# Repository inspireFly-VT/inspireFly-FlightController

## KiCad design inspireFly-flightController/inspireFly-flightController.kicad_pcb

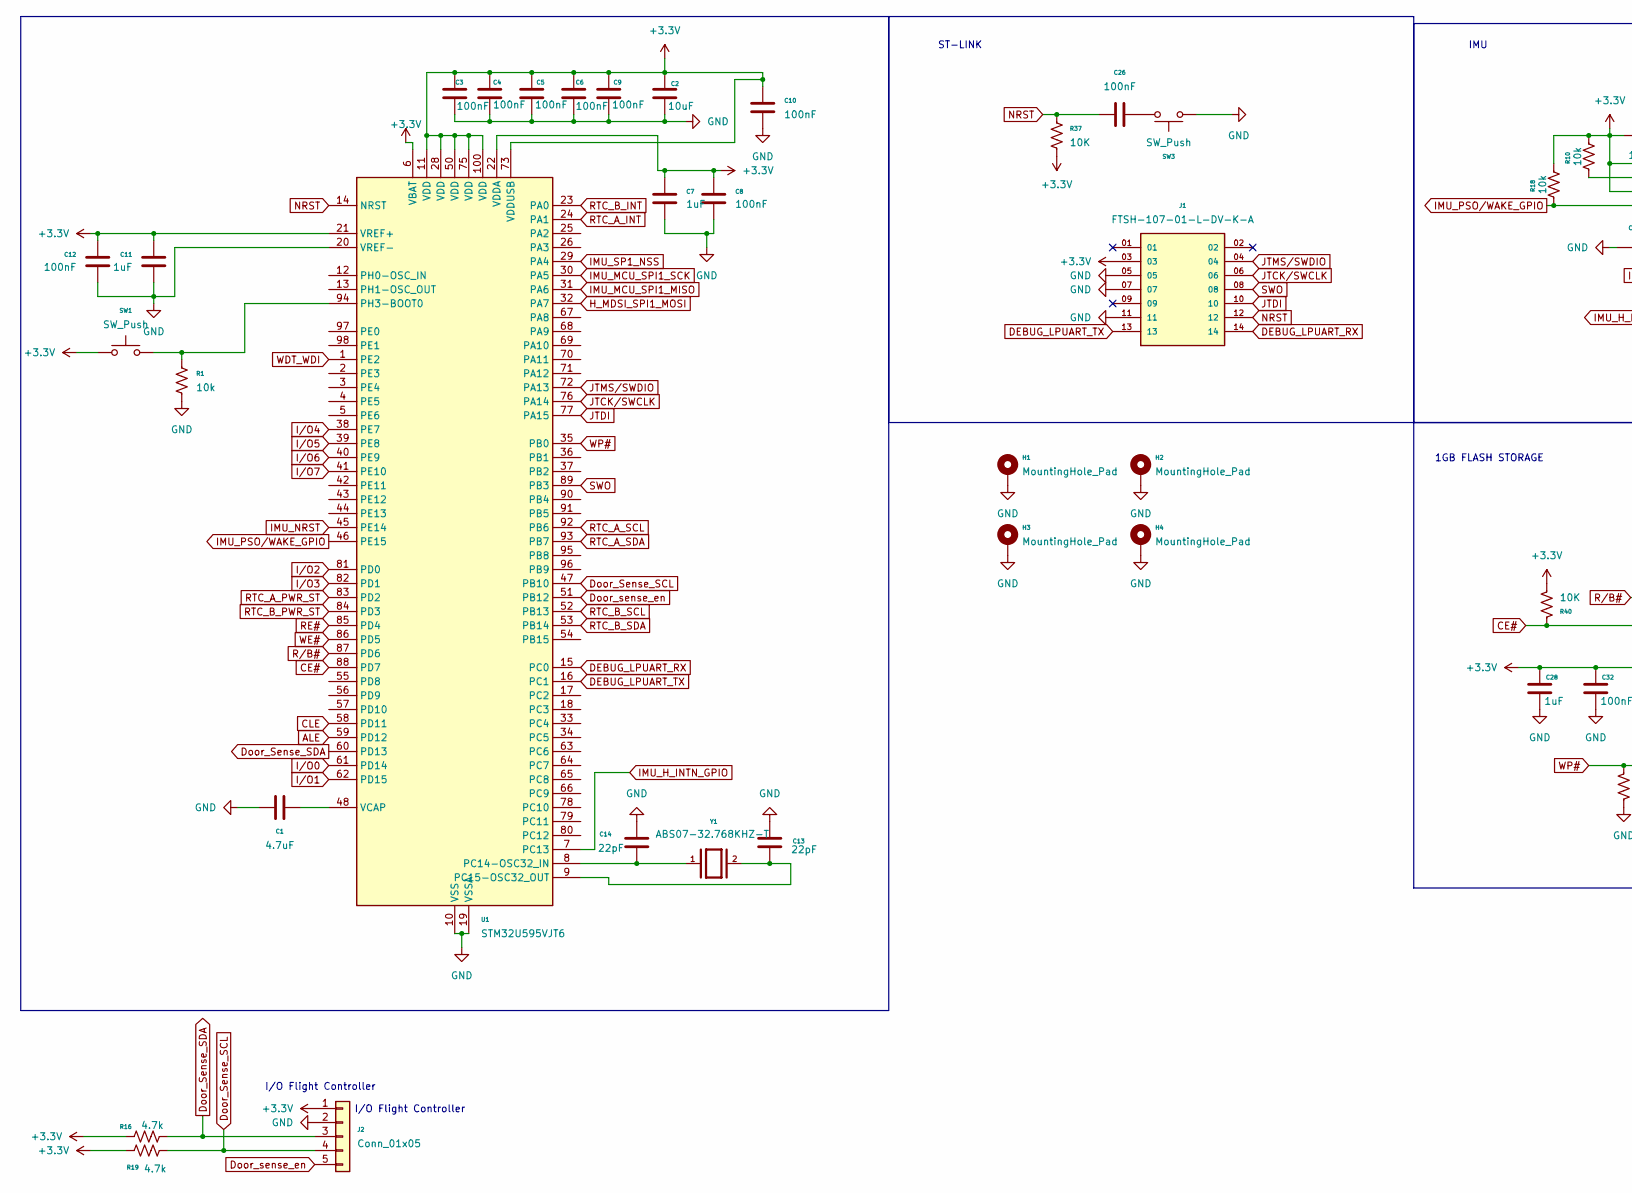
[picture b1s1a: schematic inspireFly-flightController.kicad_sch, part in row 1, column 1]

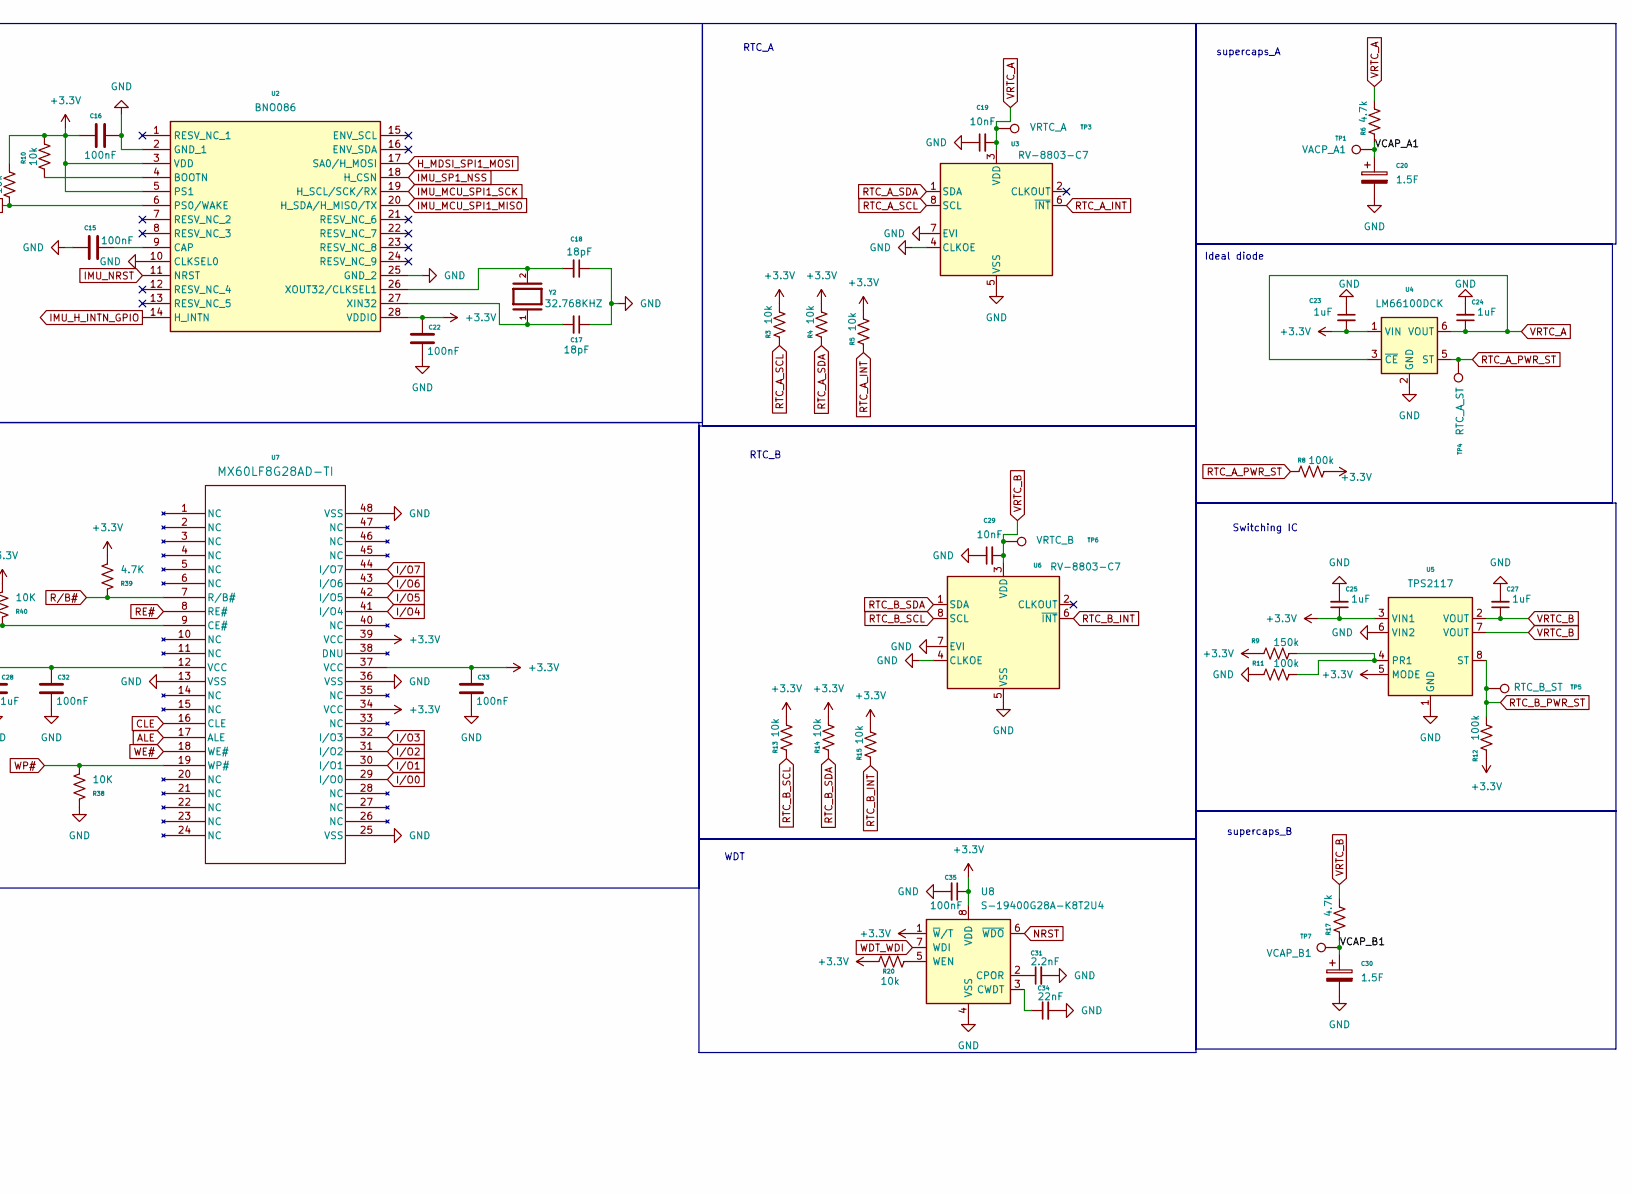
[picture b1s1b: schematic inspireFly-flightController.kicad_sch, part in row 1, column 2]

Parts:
C1: 4.7uF; C_0603_1608Metric
C2: 10uF; C_0603_1608Metric
C3, C4, C5, C6, C8, C9, C10, C12, C15, C16, C22, C26, C32, C33, C35: 100nF; C_0402_1005Metric_Pad0.74x0.62mm_HandSolder
C7, C11, C23, C24, C25, C27, C28: 1uF; C_0402_1005Metric_Pad0.74x0.62mm_HandSolder
C13, C14: 22pF; C_0402_1005Metric_Pad0.74x0.62mm_HandSolder
C17, C18: 18pF; C_0402_1005Metric_Pad0.74x0.62mm_HandSolder
C19, C29: 10nF; C_0402_1005Metric_Pad0.74x0.62mm_HandSolder
C20, C30: 1.5F; SUPERCAP_KR-5R5H155-R
C31: 2.2nF; C_0402_1005Metric_Pad0.74x0.62mm_HandSolder
C34: 22nF; C_0402_1005Metric_Pad0.74x0.62mm_HandSolder
H1, H2, H3, H4: MountingHole_Pad; MountingHole_2.2mm_M2_Pad_TopBottom
J1: FTSH-107-01-L-DV-K-A; SAMTEC_FTSH-107-01-L-DV-K-A; PARTREV H
J2: Conn_01x05; PinSocket_1x05_P2.54mm_Vertical
R1, R3, R4, R5, R10, R13, R14, R15, R18, R20: 10k; R_0402_1005Metric_Pad0.72x0.64mm_HandSolder
R6, R16, R17, R19: 4.7k; R_0402_1005Metric_Pad0.72x0.64mm_HandSolder
R8, R11, R12: 100k; R_0402_1005Metric_Pad0.72x0.64mm_HandSolder
R9: 150k; R_0402_1005Metric_Pad0.72x0.64mm_HandSolder
R37, R38, R40: 10K; R_0402_1005Metric_Pad0.72x0.64mm_HandSolder
R39: 4.7K; R_0402_1005Metric_Pad0.72x0.64mm_HandSolder
SW1, SW3: SW_Push; SW_TL1015AF160QG
TP1: VACP_A1; TestPoint_Pad_D1.5mm
TP3: VRTC_A; TestPoint_Pad_D1.5mm
TP4: RTC_A_ST; TestPoint_Pad_D1.5mm
TP5: RTC_B_ST; TestPoint_Pad_D1.5mm
TP6: VRTC_B; TestPoint_Pad_D1.5mm
TP7: VCAP_B1; TestPoint_Pad_D1.5mm
U1: STM32U595VJT6; LQFP-100_14x14mm_P0.5mm
U2: BNO086; Mouser Part Number 526-BNO086
U3, U6: RV-8803-C7; RTC_RV-8803-C7
U4: LM66100DCK; SOT-363_SC-70-6
U5: TPS2117; PWRMUX_TPS2117-DRL
U7: MX60LF8G28AD-TI; TSOPI48_MAC
U8: S-19400G28A-K8T2U4; TMSOP-8; MPN S-19400G28A-K8T2U4
Y1: ABS07-32.768KHZ-T; XTAL_ABS07-32.768KHZ-T; PARTREV 08.19.15
Y2: 32.768KHZ; XTAL_ABS07-32.768KHZ-T; PARTREV 08.19.15

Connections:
+3.3V: C2.1, C3.1, C4.1, C5.1, C6.1, C7.1, C8.1, C9.1, C10.1, C11.1, C12.1, C16.2, C22.1, C23.2, C25.1, C28.1, C32.1, C33.1, C35.1, J1.03, J2.1, R3.2, R4.2, R5.2, R8.2, R9.1, R10.1, R12.1, R13.2, R14.2, R15.2, R16.1, R18.1, R19.1, R20.1, R37.2, R39.2, R40.2, SW1.1, U1.6 (VBAT), U1.11 (VDD), U1.21 (VREF+), U1.22 (VDDA), U1.28 (VDD), U1.50 (VDD), U1.73 (VDDUSB), U1.75 (VDD), U1.100 (VDD), U2.3 (VDD), U2.5 (PS1), U2.28 (VDDIO), U4.1 (VIN), U5.3 (VIN1), U5.5 (MODE), U7.12 (VCC), U7.34 (VCC), U7.37 (VCC), U7.39 (VCC), U8.1 (~W/T), U8.8 (VDD)
/VCAP_A1: C20.1, R6.1, TP1.1 (1_1)
/VCAP_B1: C30.1, R17.1, TP7.1 (1_1)
ALE: U1.59 (PD12), U7.17 (ALE)
CE#: R40.1, U1.88 (PD7), U7.9 (CE#)
CLE: U1.58 (PD11), U7.16 (CLE)
DEBUG_LPUART_RX: J1.14, U1.15 (PC0)
DEBUG_LPUART_TX: J1.13, U1.16 (PC1)
Door_Sense_SCL: J2.4, R19.2, U1.47 (PB10)
Door_Sense_SDA: J2.3, R16.2, U1.60 (PD13)
Door_sense_en: J2.5, U1.51 (PB12)
GND: C1.1, C2.2, C3.2, C4.2, C5.2, C6.2, C7.2, C8.2, C9.2, C10.2, C11.2, C12.2, C13.1, C14.1, C15.2, C16.1, C17.1, C18.1, C19.1, C20.2, C22.2, C23.1, C24.2, C25.2, C27.2, C28.2, C29.1, C30.2, C31.2, C32.2, C33.2, C34.2, C35.2, H1.1 (1_1), H2.1 (1_1), H3.1 (1_1), H4.1 (1_1), J1.05, J1.07, J1.11, J2.2, R1.2, R11.1, R38.1, SW3.1, U1.10 (VSS), U1.19 (VSSA), U1.20 (VREF-), U1.27 (VSS), U1.49 (VSS), U1.74 (VSS), U1.99 (VSS), U2.2 (GND_1), U2.10 (CLKSEL0), U2.25 (GND_2), U3.4 (CLKOE), U3.5 (VSS), U3.7 (EVI), U4.2 (GND), U5.1 (GND), U5.6 (VIN2), U6.4 (CLKOE), U6.5 (VSS), U6.7 (EVI), U7.13 (VSS), U7.25 (VSS), U7.36 (VSS), U7.48 (VSS), U8.4 (VSS)
H_MDSI_SPI1_MOSI: U1.32 (PA7), U2.17 (SA0/H_MOSI)
IMU_H_INTN_GPIO: U1.7 (PC13), U2.14 (H_INTN)
IMU_MCU_SPI1_MISO: U1.31 (PA6), U2.20 (H_SDA/H_MISO/TX)
IMU_MCU_SPI1_SCK: U1.30 (PA5), U2.19 (H_SCL/SCK/RX)
IMU_NRST: U1.45 (PE14), U2.11 (NRST)
IMU_PSO/WAKE_GPIO: R18.2, U1.46 (PE15), U2.6 (PS0/WAKE)
IMU_SP1_NSS: U1.29 (PA4), U2.18 (H_CSN)
I/O0: U1.61 (PD14), U7.29 (I/O0)
I/O1: U1.62 (PD15), U7.30 (I/O1)
I/O2: U1.81 (PD0), U7.31 (I/O2)
I/O3: U1.82 (PD1), U7.32 (I/O3)
I/O4: U1.38 (PE7), U7.41 (I/O4)
I/O5: U1.39 (PE8), U7.42 (I/O5)
I/O6: U1.40 (PE9), U7.43 (I/O6)
I/O7: U1.41 (PE10), U7.44 (I/O7)
JTCK/SWCLK: J1.06, U1.76 (PA14)
JTDI: J1.10, U1.77 (PA15)
JTMS/SWDIO: J1.04, U1.72 (PA13)
NRST: C26.2, J1.12, R37.1, U1.14 (NRST), U8.6 (~WDO)
unnamed: C26.1, SW3.2
unnamed: C14.2, U1.8 (PC14-OSC32_IN), Y1.1
unnamed: C13.2, U1.9 (PC15-OSC32_OUT), Y1.2
unnamed: R1.1, SW1.2, U1.94 (PH3-BOOT0)
unnamed: C1.2, U1.48 (VCAP)
unnamed: R10.2, U2.4 (BOOTN)
unnamed: C15.1, U2.9 (CAP)
unnamed: C17.2, U2.27 (XIN32), Y2.1
unnamed: C18.2, U2.26 (XOUT32/CLKSEL1), Y2.2
unnamed: R9.2, R11.2, U5.4 (PR1)
unnamed: C31.1, U8.2 (CPOR)
unnamed: C34.1, U8.3 (CWDT)
unnamed: R20.2, U8.5 (WEN)
RE#: U1.85 (PD4), U7.8 (RE#)
RTC_A_INT: R5.1, U1.24 (PA1), U3.6 (~INT)
RTC_A_PWR_ST: R8.1, TP4.1 (1_1), U1.83 (PD2), U4.5 (ST)
RTC_A_SCL: R3.1, U1.92 (PB6), U3.8 (SCL)
RTC_A_SDA: R4.1, U1.93 (PB7), U3.1 (SDA)
RTC_B_INT: R15.1, U1.23 (PA0), U6.6 (~INT)
RTC_B_PWR_ST: R12.2, TP5.1 (1_1), U1.84 (PD3), U5.8 (ST)
RTC_B_SCL: R13.1, U1.52 (PB13), U6.8 (SCL)
RTC_B_SDA: R14.1, U1.53 (PB14), U6.1 (SDA)
R/B#: R39.1, U1.87 (PD6), U7.7 (R/B#)
SWO: J1.08, U1.89 (PB3)
VRTC_A: C19.2, C24.1, R6.2, TP3.1 (1_1), U3.3 (VDD), U4.3 (~CE), U4.6 (VOUT)
VRTC_B: C27.1, C29.2, R17.2, TP6.1 (1_1), U5.2 (VOUT), U5.7 (VOUT), U6.3 (VDD)
WDT_WDI: U1.1 (PE2), U8.7 (WDI)
WE#: U1.86 (PD5), U7.18 (WE#)
WP#: R38.2, U1.35 (PB0), U7.19 (WP#)

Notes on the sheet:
ST-LINK
RTC_B
supercaps_A
Switching IC
I/O Flight Controller
supercaps_B
IMU
RTC_A
WDT
Ideal diode
1GB FLASH STORAGE

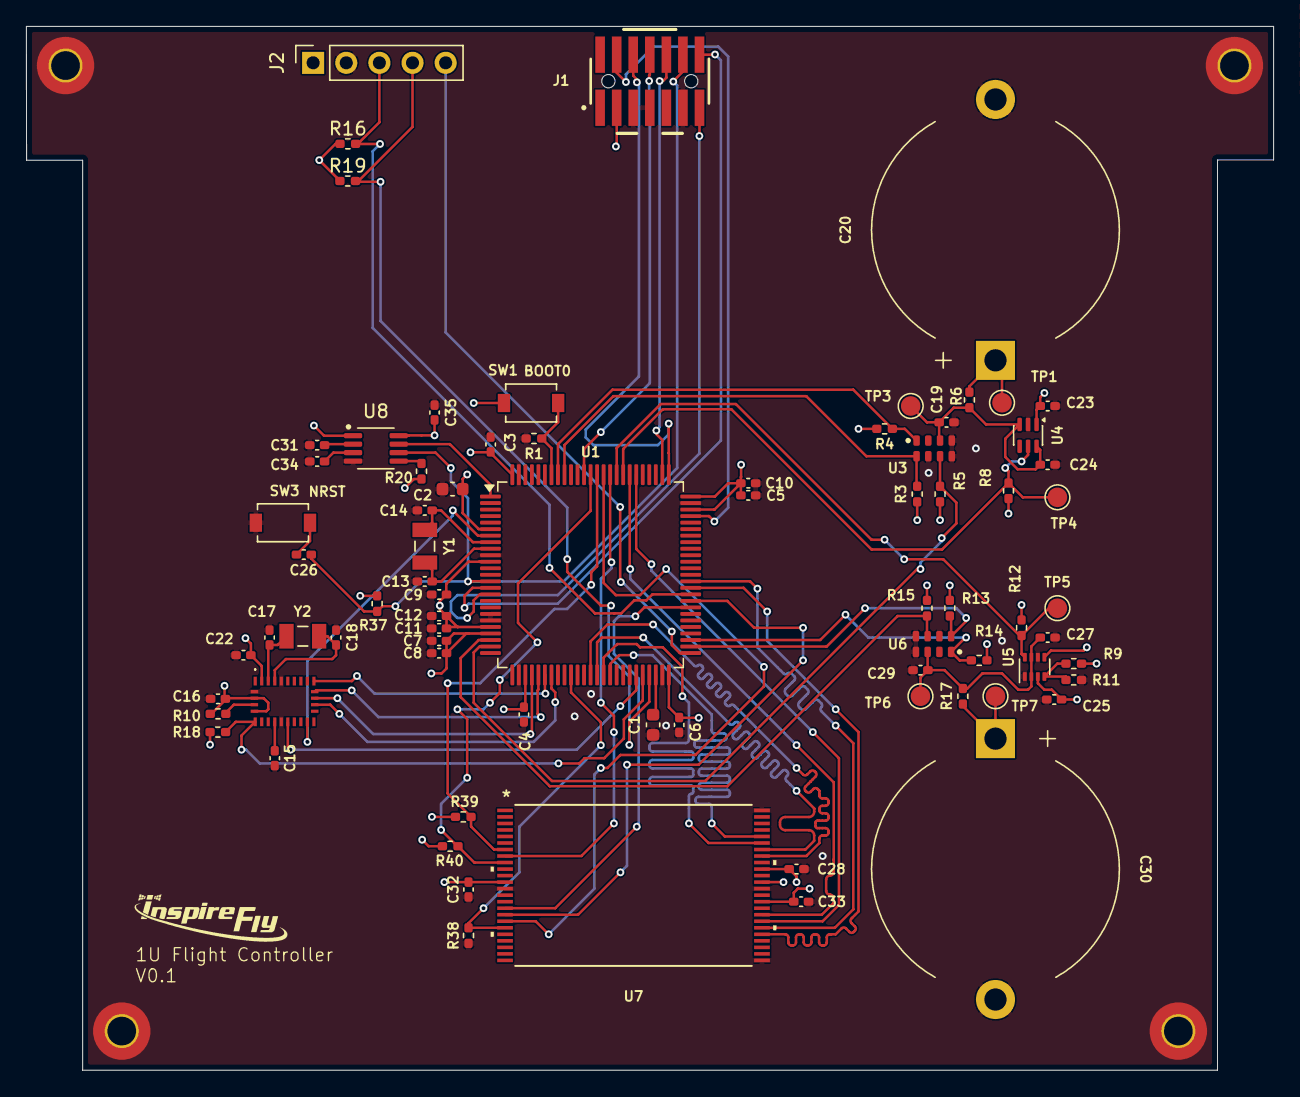
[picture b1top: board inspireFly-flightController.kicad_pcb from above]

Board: 4 copper layers, 95.6 x 80.0 mm, 80 parts (0 on the bottom side), 60 nets.

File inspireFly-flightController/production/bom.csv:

Designator,Footprint,Quantity,Value,LCSC Part #
C1,0603,1,4.7uF,
"C10, C12, C15, C16, C22, C26, C3, C32, C33, C35, C4, C5, C6, C8, C9",0402,15,100nF,
"C11, C23, C24, C25, C27, C28, C7",0402,7,1uF,
"C13, C14",0402,2,22pF,
"C17, C18",0402,2,18pF,
"C19, C29",0402,2,10nF,
C2,0603,1,10uF,
"C20, C30",SUPERCAP_KR-5R5H155-R,2,1.5F,
C31,0402,1,2.2nF,
C34,0402,1,22nF,
J1,SAMTEC_FTSH-107-01-L-DV-K-A,1,FTSH-107-01-L-DV-K-A,
J2,PinSocket_1x05_P2.54mm_Vertical,1,Conn_01x05,
"R1, R10, R13, R14, R15, R18, R20, R3, R37, R38, R4, R40, R5",0402,13,10k,
"R11, R12, R8",0402,3,100k,
"R16, R17, R19, R39, R6",0402,5,4.7k,
R9,0402,1,150k,
"SW1, SW3",SW_TL1015AF160QG,2,SW_Push,
TP1,TestPoint_Pad_D1.5mm,1,VACP_A1,
TP3,TestPoint_Pad_D1.5mm,1,VRTC_A,
TP4,TestPoint_Pad_D1.5mm,1,RTC_A_ST,
TP5,TestPoint_Pad_D1.5mm,1,RTC_B_ST,
TP6,TestPoint_Pad_D1.5mm,1,VRTC_B,
TP7,TestPoint_Pad_D1.5mm,1,VCAP_B1,
U1,LQFP-100_14x14mm_P0.5mm,1,STM32U595VJT6,
U2,BNO086,1,BNO086,
"U3, U6",RTC_RV-8803-C7,2,RV-8803-C7,
U4,SOT-363_SC-70-6,1,LM66100DCK,
U5,PWRMUX_TPS2117-DRL,1,TPS2117,
U7,TSOPI48_MAC,1,MX60LF8G28AD-TI,
U8,TMSOP-8,1,S-19400G28A-K8T2U4,S-19400G28A-K8T2U4
Y1,XTAL_ABS07-32.768KHZ-T,1,ABS07-32.768KHZ-T,
Y2,XTAL_ABS07-32.768KHZ-T,1,32.768KHZ,

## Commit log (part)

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2025-10-26 Pushing Lock
2025-11-08 added basic caps
2025-11-16 added all power caps
2025-11-19 Slight changes
    Removed cap on VBat
    Added 1uF and 100nF to VREF+
    Removed excess labels
    Cleaned up labels
2026-02-06 added Boot and crystal
2026-02-15 added 32kHz OSC
2026-02-21 added st-link connector
2026-03-01 Updated LPUART connections
    See teams message sent on 3/1
2026-03-08 added board edges
2026-03-08 updated osc cap orientation
2026-03-09 Board sizes + Layer stackup
2026-03-21 continued routing caps + updated footprints
2026-03-28 routed all power cap
2026-03-31 rerouted power caps +stlink
2026-04-04 schematic + routing for imu
2026-04-18 fixed up schematic and pcb
2026-04-26 Initial Commit
    Schematic work done and ready to be reviewed
